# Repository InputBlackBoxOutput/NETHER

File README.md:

# NETHER
Virtual reality controller for playing minecraft

## Salient features
* Modular to support addons
* Tangle free gaming since the entire system is wireless
* Minimal lag during gaming due to high-speed data transfer
* Product certifications: CE certified and ROHS compliant 

## System block diagram

## HID module

### Functions 
- Act as a wireless gateway between the modules worn by the user and the computer.
- Communicate with the computer via USB as an HID device

### 3D render: Exploded view

## Stick module

### Functions
- Connect with the HID module wirelessly
- Send data associated with a button when a button is pressed
- Read IMU data, detect striking movement and send the data to the HID module
- Calibrate the IMU device when the calibration button is pressed

### 3D render: Exploded view

## Pedometer module

### Functions
- Connect with the HID module wirelessly
- Read accelerometer data, detect steps and send the data to the HID module
- Calibrate the IMU device when the calibration button is pressed

### 3D render: Exploded view

### Made with lots of ⏱️, 📚 and ☕ by InputBlackBoxOutput

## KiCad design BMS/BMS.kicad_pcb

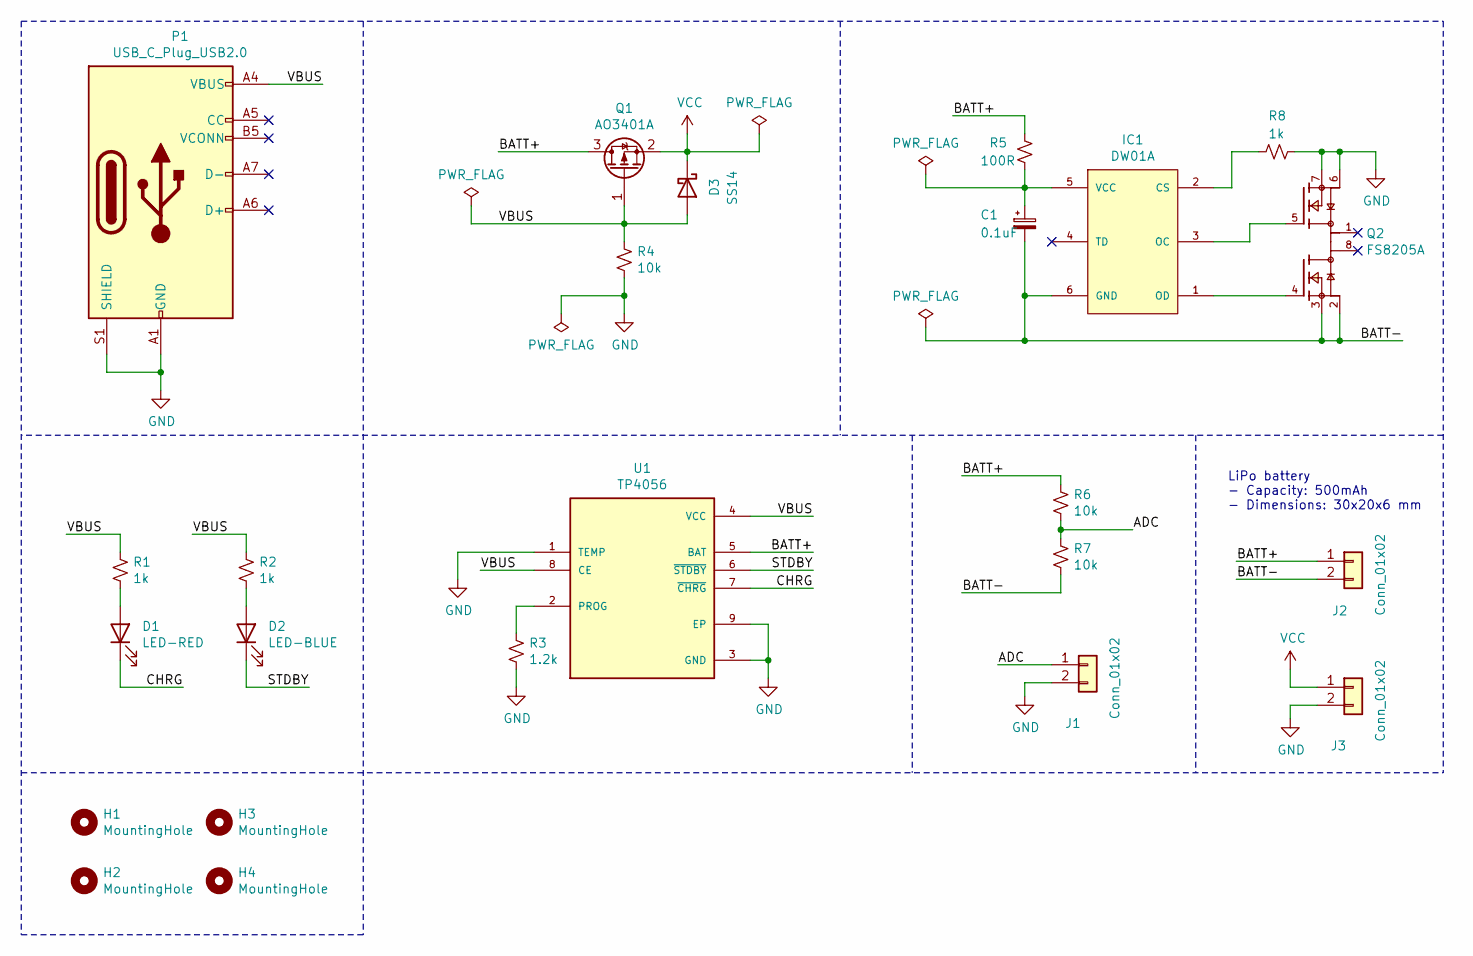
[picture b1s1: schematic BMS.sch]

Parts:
C1: 0.1uF; C_0805_2012Metric_Pad1.18x1.45mm_HandSolder
D1: LED-RED; LED_0805_2012Metric_Pad1.15x1.40mm_HandSolder
D2: LED-BLUE; LED_0805_2012Metric_Pad1.15x1.40mm_HandSolder
D3: SS14; D_SMB
H1, H2, H3, H4: MountingHole; MountingHole_2.2mm_M2
IC1: DW01A; SOT-23-6_Handsoldering; MPN DW01A; LCSC C351410
J1, J2, J3: Conn_01x02; Wire-Pad-01x02
P1: USB_C_Plug_USB2.0; USB_C_Receptacle_HRO_TYPE-C-31-M-12
Q1: AO3401A; SOT-23
Q2: FS8205A; SOP65P640X120-8N; PARTREV 1.7
R1, R2, R8: 1k; R_0805_2012Metric_Pad1.20x1.40mm_HandSolder
R3: 1.2k; R_0805_2012Metric_Pad1.20x1.40mm_HandSolder
R4, R6, R7: 10k; R_0805_2012Metric_Pad1.20x1.40mm_HandSolder
R5: 100R; R_0805_2012Metric_Pad1.20x1.40mm_HandSolder
U1: TP4056; SOP127P600X175-9N

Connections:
/ADC: J1.1, R6.2, R7.1
/BATT+: J2.1, Q1.3 (D), R5.1, R6.1, U1.5 (BAT)
/BATT-: C1.2, IC1.6 (GND), J2.2, Q2.2, Q2.3, R7.2
/CHRG: D1.1 (K), U1.7 (~CHRG)
/STDBY: D2.1 (K), U1.6 (~STDBY)
/VBUS: D3.2 (A), P1.A4 (VBUS), P1.A9 (VBUS), P1.B4 (VBUS), P1.B9 (VBUS), Q1.1 (G), R1.1, R2.1, R4.1, U1.4 (VCC), U1.8 (CE)
GND: J1.2, J3.2, P1.A1 (GND), P1.A12 (GND), P1.B1 (GND), P1.B12 (GND), P1.S1 (SHIELD), Q2.6, Q2.7, R3.2, R4.2, R8.1, U1.1 (TEMP), U1.3 (GND), U1.9 (EP)
unnamed: C1.1, IC1.5 (VCC), R5.2
unnamed: D1.2 (A), R1.2
unnamed: D2.2 (A), R2.2
unnamed: IC1.1 (OD), Q2.4
unnamed: IC1.2 (CS), R8.2
unnamed: IC1.3 (OC), Q2.5
unnamed: R3.1, U1.2 (PROG)
VCC: D3.1 (K), J3.1, Q1.2 (S)

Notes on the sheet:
LiPo battery - Capacity: 500mAh - Dimensions: 30x20x6 mm

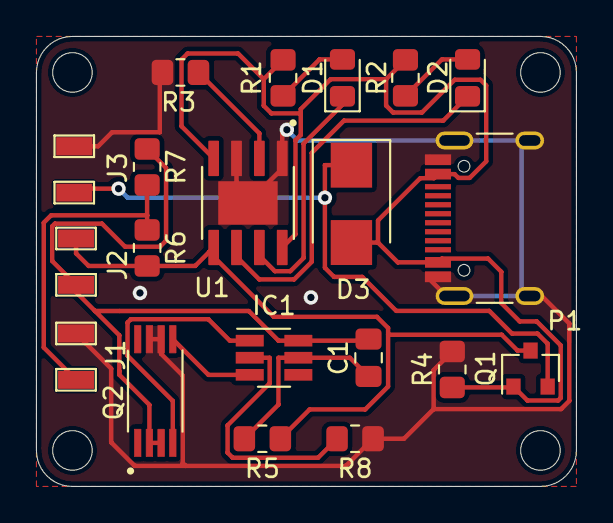
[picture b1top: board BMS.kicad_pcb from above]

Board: 2 copper layers, 30.0 x 25.0 mm, 24 parts (0 on the bottom side), 15 nets.

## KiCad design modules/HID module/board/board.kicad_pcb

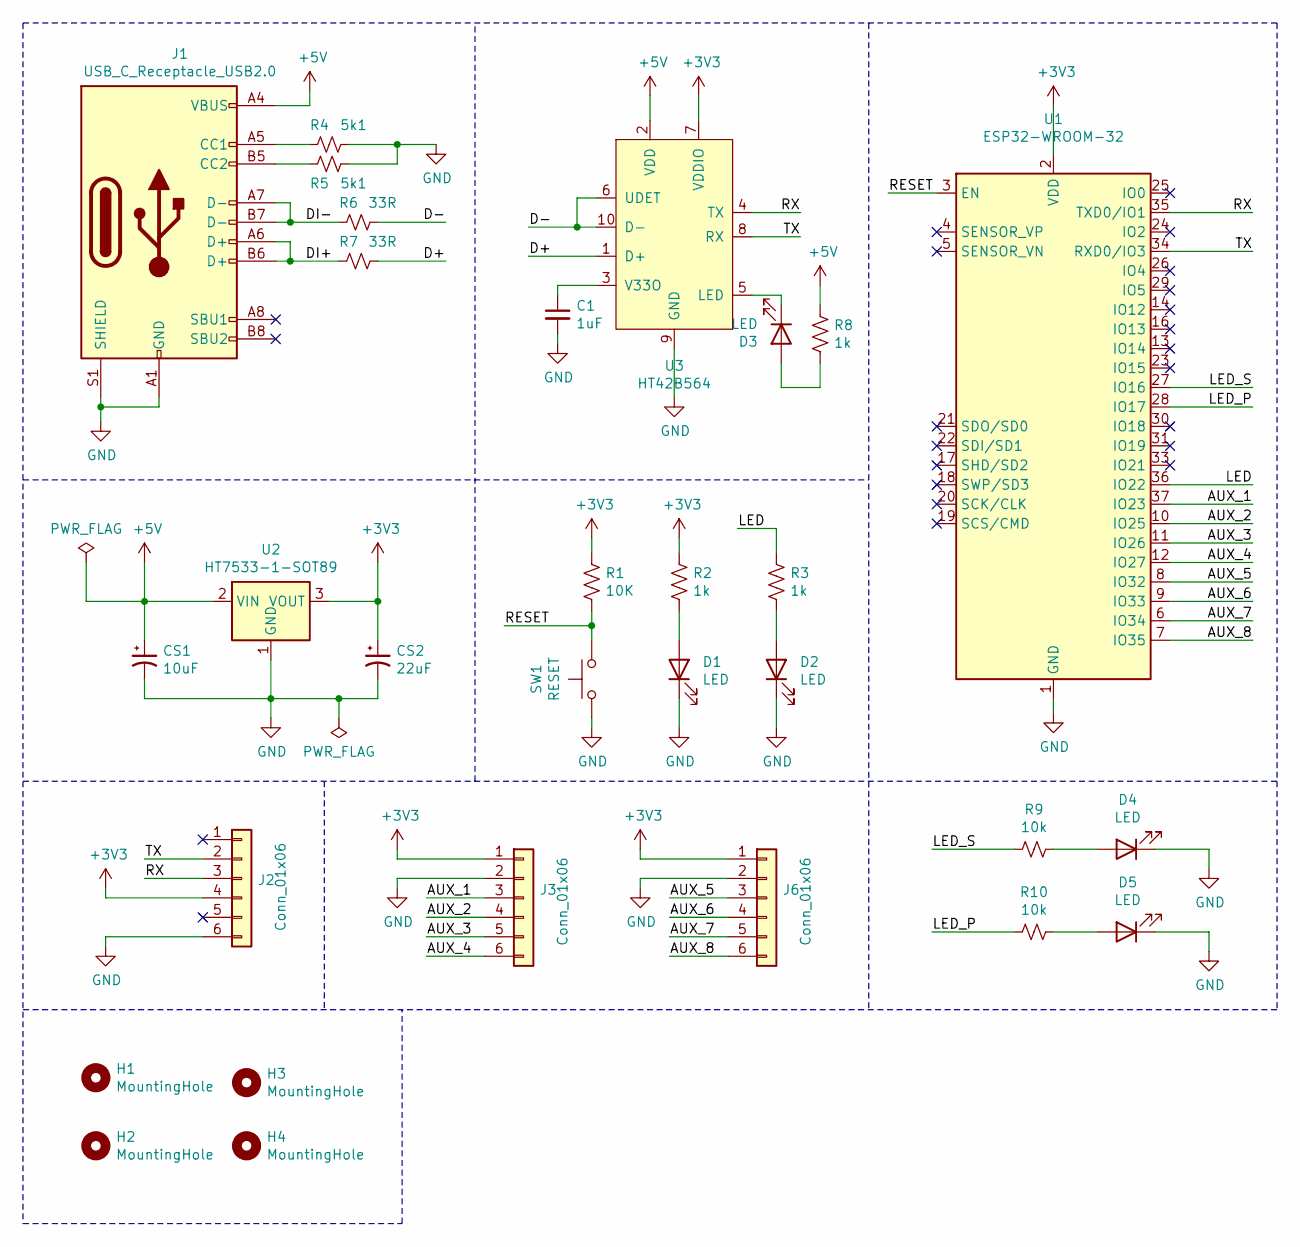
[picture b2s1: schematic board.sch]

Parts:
C1: 1uF; C_0805_2012Metric_Pad1.18x1.45mm_HandSolder
CS1: 10uF; C_0805_2012Metric_Pad1.18x1.45mm_HandSolder
CS2: 22uF; C_0805_2012Metric_Pad1.18x1.45mm_HandSolder
D1, D2, D3, D4, D5: LED; LED_0805_2012Metric_Pad1.15x1.40mm_HandSolder
H1, H2, H3, H4: MountingHole; MountingHole_2.2mm_M2
J1: USB_C_Receptacle_USB2.0; USB_C_Receptacle_HRO_TYPE-C-31-M-12
J2, J3, J6: Conn_01x06; SolderWire_1x06_P2.54mm
R1: 10K; R_0805_2012Metric_Pad1.20x1.40mm_HandSolder
R2, R3, R8: 1k; R_0805_2012Metric_Pad1.20x1.40mm_HandSolder
R4, R5: 5k1; R_0805_2012Metric_Pad1.20x1.40mm_HandSolder
R6, R7: 33R; R_0603_1608Metric_Pad0.98x0.95mm_HandSolder
R9, R10: 10k; R_0805_2012Metric_Pad1.20x1.40mm_HandSolder
SW1: RESET; SW_SPST_B3U-1000P
U1: ESP32-WROOM-32
U2: HT7533-1-SOT89; SOT-89-3
U3: HT42B564; SSOP-10_3.9x4.9mm_P1.00mm

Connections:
+3V3: CS2.1, J2.4, J3.1, J6.1, R1.1, R2.1, U1.2 (VDD), U2.3 (VOUT), U3.7 (VDDIO)
+5V: CS1.1, J1.A4 (VBUS), J1.A9 (VBUS), J1.B4 (VBUS), J1.B9 (VBUS), R8.1, U2.2 (VIN), U3.2 (VDD)
/AUX_1: J3.3, U1.37 (IO23)
/AUX_2: J3.4, U1.10 (IO25)
/AUX_3: J3.5, U1.11 (IO26)
/AUX_4: J3.6, U1.12 (IO27)
/AUX_5: J6.3, U1.8 (IO32)
/AUX_6: J6.4, U1.9 (IO33)
/AUX_7: J6.5, U1.6 (IO34)
/AUX_8: J6.6, U1.7 (IO35)
/D+: R7.1, U3.1 (D+)
/D-: R6.1, U3.6 (UDET), U3.10 (D-)
/DI+: J1.A6 (D+), J1.B6 (D+), R7.2
/DI-: J1.A7 (D-), J1.B7 (D-), R6.2
/LED: R3.1, U1.36 (IO22)
/LED_P: R10.2, U1.28 (IO17)
/LED_S: R9.2, U1.27 (IO16)
/RESET: R1.2, SW1.2, U1.3 (EN)
/RX: J2.3, U1.35 (TXD0/IO1), U3.4 (TX)
/TX: J2.2, U1.34 (RXD0/IO3), U3.8 (RX)
GND: C1.2, CS1.2, CS2.2, D1.1 (K), D2.1 (K), D4.1 (K), D5.1 (K), J1.A1 (GND), J1.A12 (GND), J1.B1 (GND), J1.B12 (GND), J1.S1 (SHIELD), J2.6, J3.2, J6.2, R4.1, R5.1, SW1.1, U1.1 (GND), U1.15 (GND), U1.38 (GND), U1.39 (GND), U2.1 (GND), U3.9 (GND)
unnamed: C1.1, U3.3 (V33O)
unnamed: D1.2 (A), R2.2
unnamed: D2.2 (A), R3.2
unnamed: D3.1 (K), U3.5 (LED)
unnamed: D3.2 (A), R8.2
unnamed: D4.2 (A), R9.1
unnamed: D5.2 (A), R10.1
unnamed: J1.A5 (CC1), R4.2
unnamed: J1.B5 (CC2), R5.2

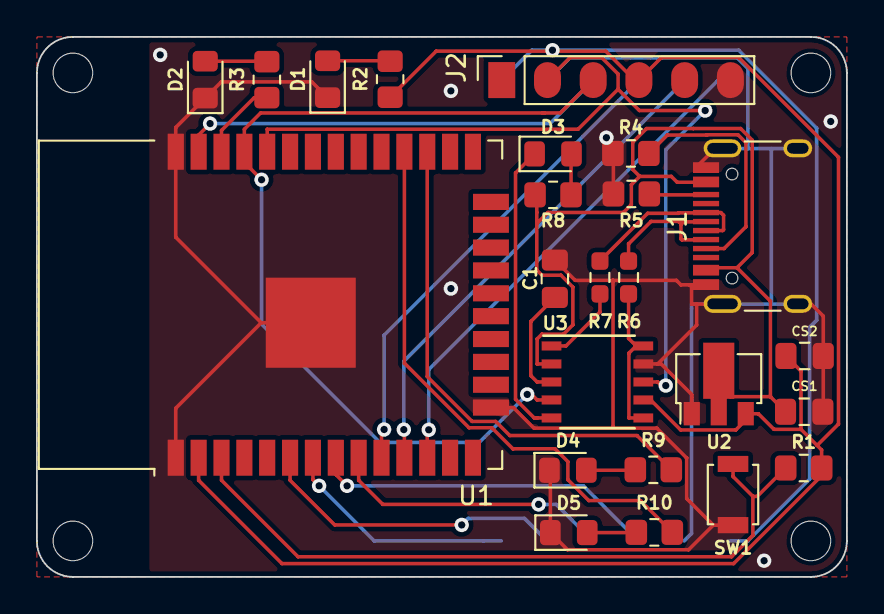
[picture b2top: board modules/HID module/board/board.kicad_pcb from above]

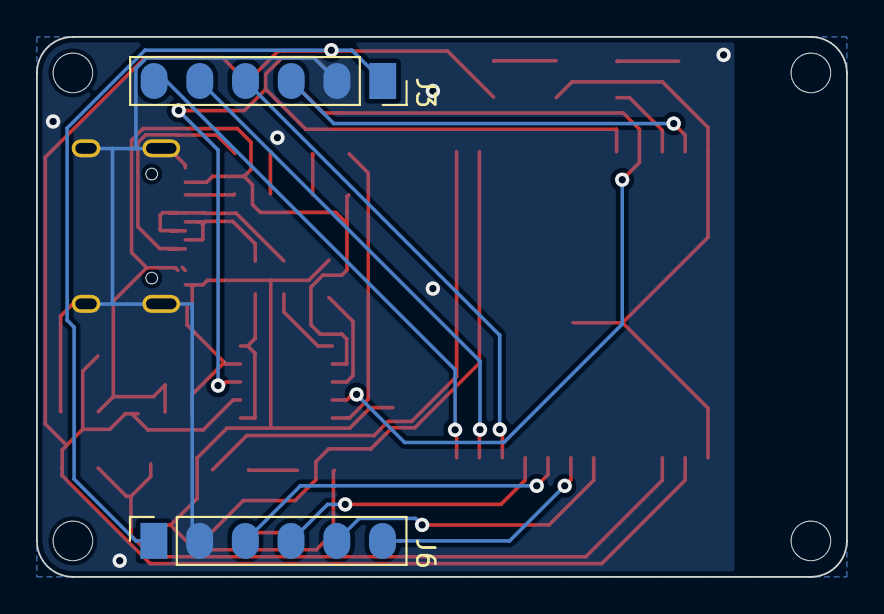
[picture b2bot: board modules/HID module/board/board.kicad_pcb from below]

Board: 2 copper layers, 45.0 x 30.0 mm, 30 parts (2 on the bottom side), 30 nets.

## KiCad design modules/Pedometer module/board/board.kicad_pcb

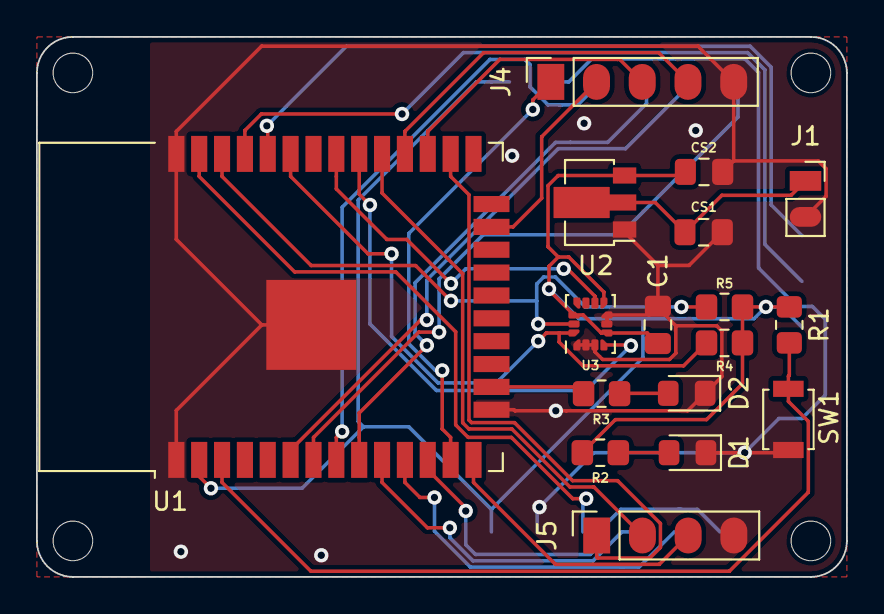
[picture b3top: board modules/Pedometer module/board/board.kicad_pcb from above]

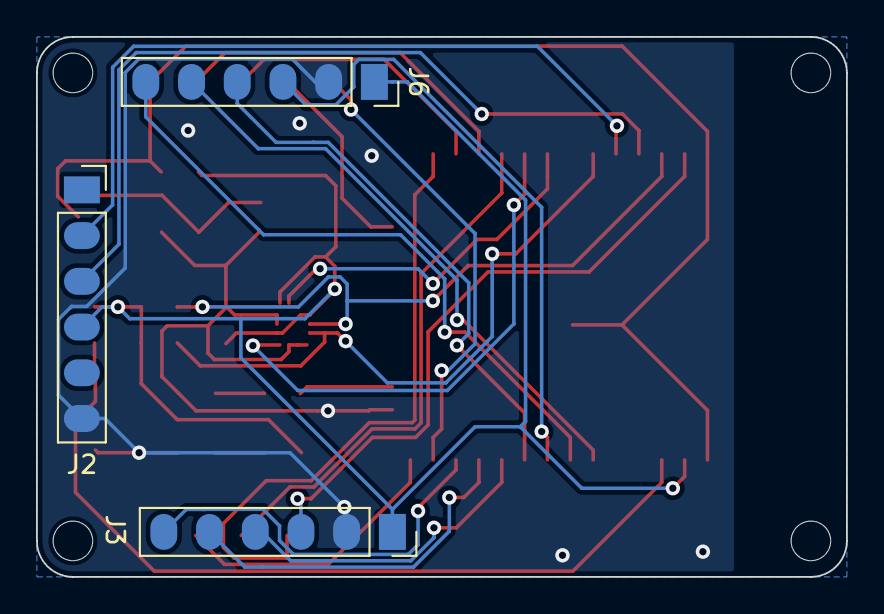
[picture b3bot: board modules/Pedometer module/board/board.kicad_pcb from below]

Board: 2 copper layers, 45.0 x 30.0 mm, 24 parts (3 on the bottom side), 28 nets.

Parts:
C1: 100nF; C_0805_2012Metric_Pad1.18x1.45mm_HandSolder
CS1: 10uF; C_0805_2012Metric_Pad1.18x1.45mm_HandSolder
CS2: 22uF; C_0805_2012Metric_Pad1.18x1.45mm_HandSolder
D1, D2: LED; LED_0805_2012Metric_Pad1.15x1.40mm_HandSolder
H1, H2, H3, H4: MountingHole; MountingHole_2.2mm_M2
J1: BATTERY; SolderWire_1x02_P2.00mm
J2, J3, J6: Conn_01x06; SolderWire_1x06_P2.54mm
J4: Conn_01x05; SolderWire_1x05_P2.54mm
J5: Conn_01x04; SolderWire_1x04_P2.54mm
R1: 10K; R_0805_2012Metric_Pad1.20x1.40mm_HandSolder
R2, R3: 1k; R_0805_2012Metric_Pad1.20x1.40mm_HandSolder
R4, R5: 10k; R_0805_2012Metric_Pad1.20x1.40mm_HandSolder
SW1: RESET; SW_SPST_B3U-1000P
U1: ESP32-WROOM-32
U2: HT7533-1-SOT89; SOT-89-3
U3: LSM6DS3; LGA-14_3x2.5mm_P0.5mm_LayoutBorder3x4y

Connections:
+3V3: C1.1, CS2.1, J2.4, J3.1, J6.1, R1.1, R2.1, R4.1, R5.1, U1.2, U2.3, U3.5, U3.8, U3.12
+3V8: CS1.1, J1.1, U2.2
/1_1: J4.1, U1.13
/1_2: J4.2, U1.23
/1_3: J4.3, U1.27
/1_4: J4.4, U1.28
/2_1: J5.1, U1.26
/2_2: J5.2, U1.29
/2_3: J5.3, U1.14
/AUX_1: J3.3, U1.37
/AUX_2: J3.4, U1.10
/AUX_3: J3.5, U1.11
/AUX_4: J3.6, U1.12
/AUX_5: J6.3, U1.8
/AUX_6: J6.4, U1.9
/AUX_7: J6.5, U1.6
/AUX_8: J6.6, U1.7
/LED: R3.1, U1.16
/RESET: R1.2, SW1.2, U1.3
/RX: J2.3, U1.35
/TX: J2.2, U1.34
GND: C1.2, CS1.2, CS2.2, D1.1, D2.1, J1.2, J2.6, J3.2, J4.5, J5.4, J6.2, SW1.1, U1.1, U1.15, U1.38, U1.39, U2.1, U3.1, U3.2, U3.3, U3.6, U3.7
INT1: U1.30, U3.4
INT2: U1.31, U3.9
unnamed: D1.2, R2.2
unnamed: D2.2, R3.2
SCL: R5.2, U1.36, U3.13
SDA: R4.2, U1.33, U3.14

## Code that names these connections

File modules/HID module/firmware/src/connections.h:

// AUX GPIO: Added for future extension and not used
// The ADC channel connected to pin 35 can be used to check LiPo battery voltage

#ifndef CONNECTIONS_H
#define CONNECTIONS_H

#define LED_S   16
#define LED_P   17

#define LED     22

#define AUX_1   23
#define AUX_2   25
#define AUX_3   26
#define AUX_4   27
#define AUX_5   32  // ADC
#define AUX_6   33  // ADC
#define AUX_7   34  // ADC
#define AUX_8   35  // ADC

#endif //CONNECTIONS_H

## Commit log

2022-12-21 BMS design files added
2022-12-21 README: Information added
2022-12-25 Stick module: PCB design files added
2022-12-25 Pedometer module: PCB design files added
2022-12-26 HID module: PCB design files added
2022-12-28 README: Exploded view added + Datasheets added
2022-12-28 README: Minor changes
2022-12-31 Fix I2C pullup resistor
2023-01-02 Enclosure design files
2023-02-04 PCB: USB C receptacle moved close to PCB edge
2023-02-06 Stick module: Button PCB
2023-02-06 Firmware
